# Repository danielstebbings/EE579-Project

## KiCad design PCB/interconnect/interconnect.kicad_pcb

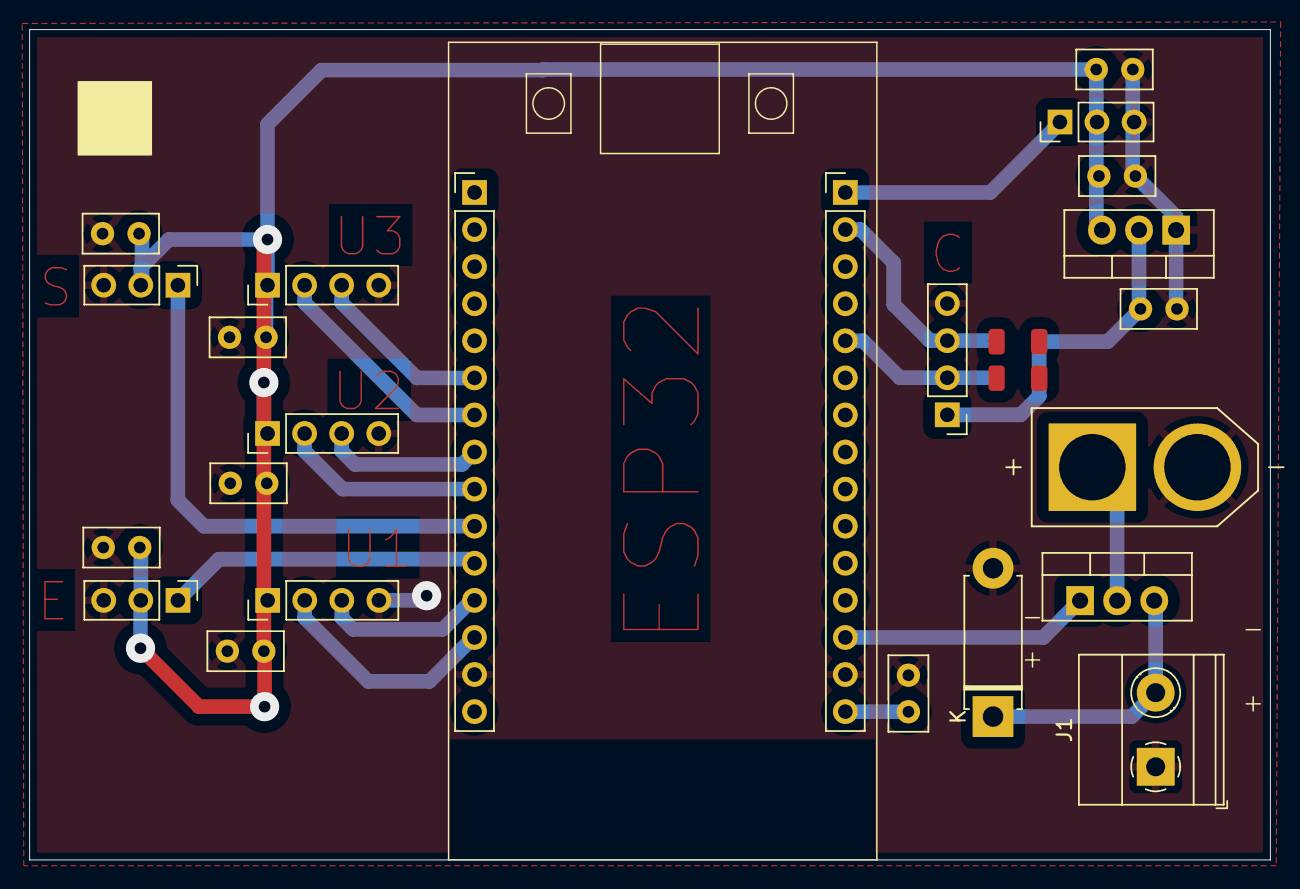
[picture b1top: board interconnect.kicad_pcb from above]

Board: 2 copper layers, 85.0 x 56.9 mm, 25 parts (0 on the bottom side), 17 nets.

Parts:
C201, C202, C203, C302, C501, C601, C701: 1uF; C_Disc_D5.0mm_W2.5mm_P2.50mm
C401: 22uF; C_Disc_D5.0mm_W2.5mm_P2.50mm
C402: 10uF; C_Disc_D5.0mm_W2.5mm_P2.50mm
D201: SM4007PL; D_5W_P10.16mm_Horizontal
J1: 5.08mm Screw Terminal; TerminalBlock_Phoenix_MKDS-1,5-2-5.08_1x02_P5.08mm_Horizont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
J201: XT60-M; AMASS_XT60-M
J203, J204, J205: Conn_01x03; PinHeader_1x03_P2.54mm_Vertical
J206, J501, J601, J701: Conn_01x04; PinHeader_1x04_P2.54mm_Vertical
J301, J302: Conn_01x15; PinHeader_1x15_P2.54mm_Vertical
Q1: IPP060N06N; TO-220-3_Vertical
R301, R302: 4.7kΩ; R_1206
U1: LM317_TO-220; TO-220-3_Vertical

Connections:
+3V3: C302.1, C401.1, J206.1, J302.15, R301.1, R302.1, U1.2 (VO)
+5V: C201.1, C202.1, C203.1, C402.1, C501.1, C601.1, C701.1, J203.2, J204.2, J205.2, J501.1, J601.1, J701.1, U1.3 (VI)
/Connectors/MOTORS.ESC: J203.1, J301.11
/Connectors/MOTORS.Magnet: J205.1, J302.1
/Connectors/MOTORS.Steering: J204.1, J301.10
/Connectors/Magnet_+: D201.1, J1.2, Q1.3 (S)
/Connectors/Motor_Batt_+: J201.P (POS), Q1.2 (D)
/Connectors/ULTRASONICS.US1_ECHO: J301.12, J701.3
/Connectors/ULTRASONICS.US1_TRIGG: J301.13, J701.2
/Connectors/ULTRASONICS.US2_ECHO: J301.8, J601.3
/Connectors/ULTRASONICS.US2_TRIGG: J301.9, J601.2
/Connectors/ULTRASONICS.US3_ECHO: J301.6, J501.3
/Connectors/ULTRASONICS.US3_TRIGG: J301.7, J501.2
/Connectors/XIAO.SCL: J206.3, J302.2, R301.2
/Connectors/XIAO.SDA: J206.2, J302.5, R302.2
/MCUs/ESP32_D15: J302.13, Q1.1 (G)
GND: C201.2, C202.2, C203.2, C302.2, C401.2, C402.2, C501.2, C601.2, C701.2, D201.2, J1.1, J201.N (NEG), J203.3, J204.3, J205.3, J206.4, J301.14, J302.14, J501.4, J601.4, J701.4, U1.1 (ADJ)

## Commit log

2025-02-07 created folder
2025-02-07 rename
2025-02-17 ai dev
2025-02-17 py reqss
2025-02-17 32 Epoch run
2025-02-18 created logan testing branch and merged files
2025-04-19 Working on getting it going
2025-04-28 getting things ironed out
2025-05-01 aye aye ai
2025-05-01 updated gitignore to ignore venv env vscode and build
2025-05-01 ultrasonic working
2025-05-01 func update
2025-05-01 pushing PCB + AI training stuffs
2025-05-02 PCB Rev 1
2025-05-02 Order
2025-05-02 i2c master setup and some channel defs
2025-05-03 i2c changes
2025-05-04 i2c slave fix and ultrasonic now non blocking
2025-05-04 i2c working
2025-05-05 Model building and flashing. Need camera integration + preloaded image testing
2025-05-07 Camera is photo-ing, working on saving to sd card. SD. Need to test to make sure that the classification is fine!
2025-05-07 Added some line comments - bug to fix
2025-05-08 Working can model with 250 epoch, can only v1
2025-05-08 Updated PCB, working inference
2025-05-08 i2c fixed
2025-05-08 latest 23:55
2025-05-09 latest up to date new pins pls dont block pls and thanks
2025-05-09 bbox normalise function
2025-05-09 Working with i2C tx and 1200 epoch model
2025-05-09 push latest states - Logan
2025-05-13 Harness Diagram
